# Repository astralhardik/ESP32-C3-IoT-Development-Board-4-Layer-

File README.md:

# ESP32-C3 IoT Development Board (4-Layer)

## 📋 Project Overview

This repository contains the hardware design files (KiCad) for a custom **4-layer IoT Development Board** powered by the **ESP32-C3-WROOM-02** module. 

Designed this compact board is an all-in-one solution for environmental sensing and data logging. It integrates power management for LiPo batteries, a suite of sensors (Environmental, Light, Audio), and dual storage options (SD Card + External Flash), making it ideal for low-power edge computing applications.

## ✨ Key Features

*   **Microcontroller**: ESP32-C3-WROOM-02 (RISC-V 32-bit, WiFi 4 + Bluetooth 5 LE).
*   **4-Layer PCB**: Optimized stack-up for signal integrity and compact routing.
*   **Power System**: 
    *   **USB-C** for power and programming.
    *   **MCP73871** Li-Ion/Li-Poly Battery Charger with System Load Sharing (allows simultaneous charging and system operation).
    *   **LM1117-3.3** LDO for stable 3.3V regulation.
*   **Onboard Sensors**:
    *   **BME280**: Temperature, Humidity, and Barometric Pressure (I2C).
    *   **MAX4466**: Electret Microphone with Preamplifier (Analog Output).
    *   **TEMT6000**: Ambient Light Sensor (Analog Photo-transistor).
*   **Storage**:
    *   **MicroSD Card Slot** (SPI mode).
    *   **W25Q32** 32M-bit (4MB) External SPI Flash for logging/OTA.
*   **Connectivity**:
    *   **CP2102N** USB-to-UART Bridge with Auto-Program/Reset circuit (DTR/RTS logic).
    *   **I2C Header**: JST/Pin header for external OLED displays or sensors.

## 🔧 Hardware Specifications

| Component | Part Number | Interface | Description |
|-----------|-------------|-----------|-------------|
| **MCU Module** | ESP32-C3-WROOM-02-H4 | UART/SPI/I2C | Core processor, 4MB integrated flash |
| **USB Bridge** | CP2102N | USB 2.0 | USB to Serial converter |
| **Env. Sensor** | BME280 | I2C (Add: 0x76) | Precision Temp/Hum/Press |
| **Audio Amp** | MAX4466 | Analog (ADC) | Mic preamp with adjustable gain |
| **Light Sensor** | TEMT6000 | Analog (ADC) | Visible light spectrum sensor |
| **Charger** | MCP73871 | - | 1A Battery charger with Power Path |
| **Ext. Flash** | W25Q32JV | SPI | Additional 32Mbit storage |

## 🔌 Pinout & Interfaces

### User Interface (UI)
*   **Boot Button (SW1)**: Connected to GPIO9 (Strapping pin).
*   **Reset Button (SW2)**: Connected to EN (Enable).
*   **LED Indicators**: 
    *   Charging (Red)
    *   Charged (Green)
    *   Power/User (Blue)

### Expansion Headers
*   **J4 (I2C)**: `3V3`, `SDA`, `SCL`, `GND` - Designed for 0.96" OLED displays.
*   **J5 (GPIO)**: Breakout for spare GPIOs (GPIO8, GPIO18, GPIO19).

## 🛠️ Schematics

### Power Management
The power stage uses the **MCP73871** to manage USB and Battery power seamlessy. An **LM1117-3.3** provides the system voltage.

### Sensor Array
The board features a BME280 for environment data, a MAX4466 for audio processing, and a TEMT6000 for light detection.

### MCU & Storage
The ESP32-C3 is the heart of the board, interfacing with the SD Card and Flash memory via SPI.

## 🚀 Getting Started

1.  **Clone the repository**:
    ```
    git clone https://github.com/yourusername/ESP32-C3-IoT-Board.git
    ```
2.  **Open the Hardware Design**:
    *   Install [KiCad 9.0+](https://www.kicad.org/).
    *   Open `ESP32 project/ESP32 project.kicad_pro`.
3.  **Firmware Development**:
    *   The board uses the **CP2102N** bridge. Ensure drivers are installed.
    *   **PlatformIO / Arduino IDE**: Select board **"ESP32C3 Dev Module"**.
    *   **Auto-Upload**: The board includes the standard transistor reset logic, so no manual button pressing is required to upload code.

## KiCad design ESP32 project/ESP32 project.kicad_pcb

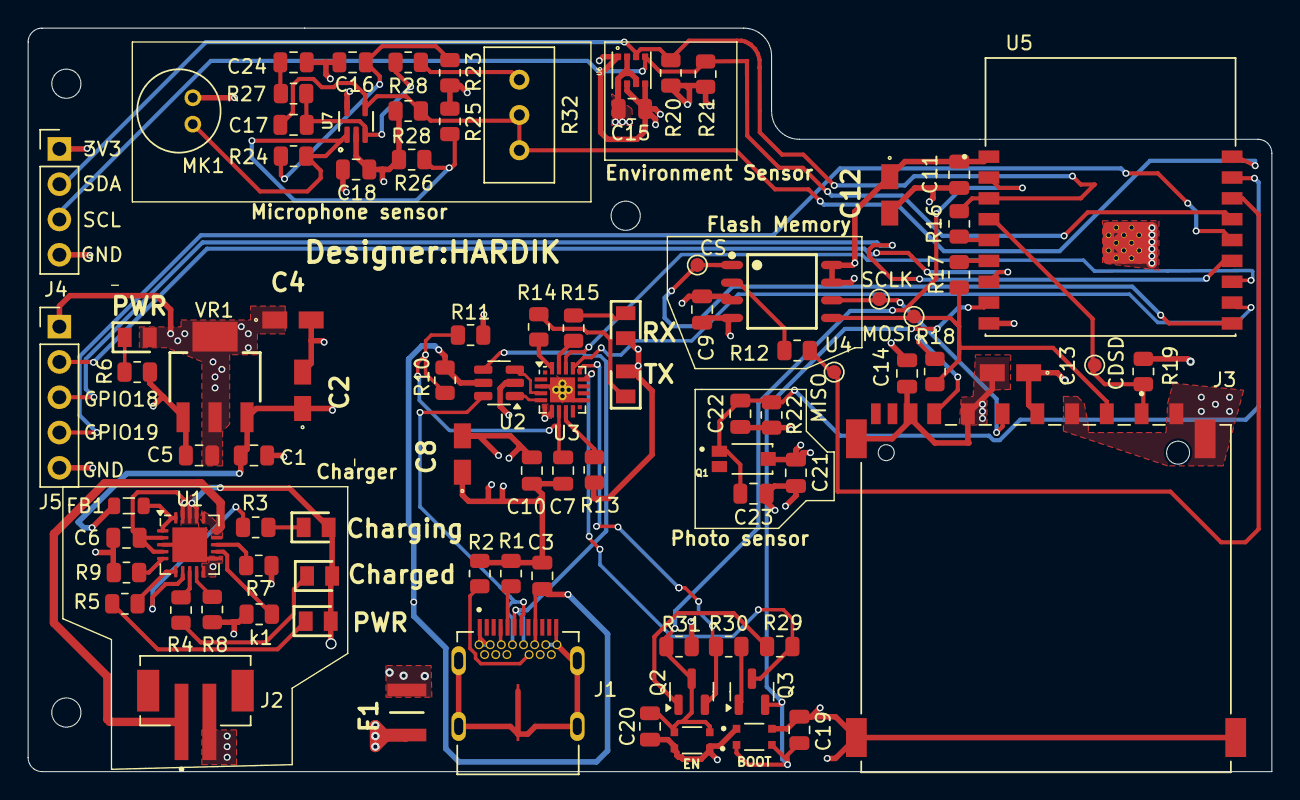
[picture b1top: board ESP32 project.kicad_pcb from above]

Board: 4 copper layers, 89.5 x 53.5 mm, 90 parts (0 on the bottom side), 60 nets.

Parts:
BOOT: Boot; SW_USLPT2819DT2TR
C1, C3, C5, C10, C15, C16, C17, C18, C19, C21: 0.1u; C_0805_2012Metric
C2, C4: 10u; T491A
C6, C20: 1u; C_0805_2012Metric
C7: 1uf; C_0805_2012Metric
C8: 4.7u; T491A
C9, C11, C14: 0.1U; C_0805_2012Metric
C12, C13: 10U; T491A
C22, C23: 10n; C_0805_2012Metric
C24: 10u; C_0805_2012Metric
CDSD: Test CS_SD; TestPoint_Pad_D1.0mm
CS: Test CS; TestPoint_Pad_D1.0mm
Charged: LTST-C170GKT; LEDC2012X120N
Charging: LTST-C170TBKT; LEDC2012X120N
EN: Reset; SW_USLPT2819DT2TR
F1: 0ZCH0110AF2E; FUSC3226X100N
FB1: FerriteBead; L_0805_2012Metric
J1: SS-52400-002; BELFUSE_SS-52400-002
J2: B2B-PH-SM4-TB; JST_B2B-PH-SM4-TB
J3: GSD090012SEU; AMPHENOL_GSD090012SEU
J4: Conn_01x04_Pin; PinHeader_1x04_P2.54mm_Vertical
J5: Conn_01x05_Pin; PinHeader_1x05_P2.54mm_Vertical
MISO: Test MISO; TestPoint_Pad_D1.0mm
MK1: CMC-5042PF-AC; CUI_CMC-5042PF-AC
MOSI: Test MOSI; TestPoint_Pad_D1.0mm
PWR: LTST-C170KRKT; LEDC2012X120N
PWR#2: LTST-C170KRKT; LEDC2012X120N
Q1: TEMT6000X01; TRANS_TEMT6000X01
Q2, Q3: BC817; SOT-23
R1, R2: 5k1; R_0805_2012Metric
R3, R4, R5, R6, R14, R15: 470; R_0805_2012Metric
R7: 2k; R_0805_2012Metric
R8, R9, R22: 10k; R_0805_2012Metric
R10: 22k1; R_0805_2012Metric
R11: 47k5; R_0805_2012Metric
R12, R16, R17, R18: 50; R_0805_2012Metric
R13, R27: 1k; R_0805_2012Metric
R19, R29, R30, R31: 10K; R_0805_2012Metric
R20, R21: 4k7; R_0805_2012Metric
R23, R24: 2K; R_0805_2012Metric
R25, R26: 1M; R_0805_2012Metric
R28: 100K; R_0805_2012Metric
R28#2: 22k; R_0805_2012Metric
R32: 35WR100KLFTR; Potentiometer_Bourns_3296W_Vertical
RX: LTST-C170KRKT; LEDC2012X120N
SCLK: Test SCLK; TestPoint_Pad_D1.0mm
TX: LTST-C170GKT; LEDC2012X120N
U1: MCP73871; QFN-20-1EP_4x4mm_P0.5mm_EP2.5x2.5mm
U2: USBLC6-2SC6; SOT-23-6
U3: CP2102N-Axx-xQFN20; SiliconLabs_QFN-20-1EP_3x3mm_P0.5mm_EP1.8x1.8mm_ThermalVias
U4: W25Q32JVSSIQ; SOIC127P790X216-8N
U5: ESP32-C3-WROOM-02-H4; MODULE_ESP32-C3-WROOM-02-H4
U6: BME280; PSON65P250X250X100-8N
U7: MAX4466EXK; SOT65P210X110-5N
VR1: LM1117MPX-3.3; VREG_LM1117MPX-3.3
k1: 20k; R_0805_2012Metric

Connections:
+3.3V: C4.1, C5.1, C8.2, C9.1, C10.2, C11.1, C12.1, C13.1, C14.1, C15.1, C18.1, C21.2, J3.4 (VDD1), J4.1, J5.1, PWR#2.2 (A), Q1.3, R13.1, R19.1, R20.1, R21.1, R23.1, R25.1, R31.1, RX.2 (A), TX.2 (A), U3.6 (VDD), U3.7 (VREGIN), U4.3 (~WP(IO2)), U4.7 (~HOLD/~RESET(IO3)), U4.8 (VCC), U5.1 (3V3), U6.2 (CSB), U6.6 (VDDIO), U6.8 (VDD), U7.5 (VCC), VR1.2 (VOUT_2), VR1.4 (VOUT_4)
+5V: C1.1, C2.1, FB1.2, VR1.3 (VIN)
/+5v_USB: C6.1, Charged.2 (A), Charging.2 (A), F1.2, PWR.2 (A), U1.2 (VPCC), U1.4 (PROG2), U1.17 (CE), U1.18 (IN), U1.19 (IN)
/ESP32-C3-02/BOOT: BOOT.3 (B0), BOOT.4 (B1), C19.1, Q3.2 (E), U5.8 (IO9)
/ESP32-C3-02/CD_SD: CDSD.1, J3.1 (CD/DAT3), R19.2, U5.4 (IO5)
/ESP32-C3-02/CS: CS.1, U4.1 (~CS), U5.10 (IO10)
/ESP32-C3-02/CTS: Q3.3 (C), R29.1, U3.15 (~CTS)
/ESP32-C3-02/EN: C20.1, EN.3 (B0), EN.4 (B1), Q2.3 (C), R31.2, U5.2 (EN)
/ESP32-C3-02/GPIO8: J5.2, U5.7 (IO8)
/ESP32-C3-02/GPIO18: J5.3, U5.13 (IO18)
/ESP32-C3-02/GPIO19: J5.4, U5.14 (IO19)
/ESP32-C3-02/MIC_OUT: C17.2, R28.2, R32.1, R32.2, U5.18 (IO0), U7.4 (OUT)
/ESP32-C3-02/MISO_DO: MISO.1, R12.2, U5.16 (IO2)
/ESP32-C3-02/MOSI_DI: J3.2 (CMD), MOSI.1, R17.1, R18.1, U4.5 (DI(IO0))
/ESP32-C3-02/PHOTO_C: C22.1, C23.1, Q1.1, R22.1, U5.17 (IO1)
/ESP32-C3-02/RTS: Q2.2 (E), R30.1, U3.16 (~RTS)
/ESP32-C3-02/RX_TX: U3.17 (RXD), U5.11 (RXD)
/ESP32-C3-02/SCL: J4.3, R21.2, U5.15 (IO3), U6.4 (SCK)
/ESP32-C3-02/SCLK: J3.5 (CLK), SCLK.1, U4.6 (CLK)
/ESP32-C3-02/SDA: J4.2, R16.1, R20.2, U5.3 (IO4), U6.3 (SDI)
/ESP32-C3-02/TX_RX: U3.18 (TXD), U5.12 (TXD)
/ESP32-C3-02/USB_D+: U2.3 (I/O2), U3.4 (D+)
/ESP32-C3-02/USB_D-: U2.1 (I/O1), U3.5 (D-)
/USB_DN: J1.A7 (DN1), J1.B7 (DN2), U2.6 (I/O1)
/USB_DP: J1.A6 (DP1), J1.B6 (DP2), U2.4 (I/O2)
/VBAT: J2.1, U1.14 (V_{BAT}), U1.15 (V_{BAT}), U1.16 (V_{BAT_SENSE})
/vBUS: C3.1, F1.1, J1.A4 (VBUSA1), J1.A9 (VBUSA2), J1.B4 (VBUSB1), J1.B9 (VBUSB2), R10.1, U2.5 (VBUS)
GND: BOOT.1 (A0), BOOT.2 (A1), C1.2, C2.2, C3.2, C4.2, C5.2, C6.2, C7.2, C8.1, C9.2, C10.1, C11.2, C12.2, C13.2, C14.2, C15.2, C16.1, C18.2, C19.2, C20.2, C21.1, C22.2, C23.2, C24.1, EN.1 (A0), EN.2 (A1), J1.A1 (GNDA1), J1.A12 (GNDA2), J1.B1 (GNDB1), J1.B12 (GNDB2), J1.G1 (GND/SHIELD), J1.G2 (GND/SHIELD), J1.G3 (GND/SHIELD), J1.G4 (GND/SHIELD), J1.S1 (GND/SHIELD), J1.S2 (GND/SHIELD), J1.S3 (GND/SHIELD), J1.S4 (GND/SHIELD), J2.2, J3.3 (VSS1), J3.6 (VSS2), J3.8 (DAT1), J3.9 (DAT2), J3.G1 (SHIELD_GND), J3.G2 (SHIELD_GND), J3.G3 (SHIELD_GND), J3.G4 (SHIELD_GND), J4.4, J5.5, MK1.GND, R1.2, R2.2, R6.2, R7.1, R8.2, R9.1, R11.2, R22.2, R26.2, R28.1, U1.3 (SEL), U1.10 (V_{SS}), U1.11 (V_{SS}), U1.21 (V_{SS}), U2.2 (GND), U4.4 (GND), U5.9 (GND), U5.19 (GND), U5.20 (GND), U5.21 (GND), U5.22 (GND), U5.23 (GND), U5.24 (GND), U5.25 (GND), U5.26 (GND), U5.27 (GND), U5.28 (GND), U5.29 (GND), U5.30 (GND), U5.31 (GND), U5.32 (GND), U5.33 (GND), U5.34 (GND), U5.35 (GND), U5.36 (GND), U5.37 (GND), U5.38 (GND), U5.39 (GND), U6.1 (GND), U6.5 (SDO), U6.7 (GND), U7.2 (GND), VR1.1 (GND), k1.1
unnamed: C16.2, R23.2, R24.1
unnamed: C24.2, R27.1
unnamed: FB1.1, U1.1 (OUT), U1.20 (OUT)
unnamed: J1.A5 (CC1), R1.1
unnamed: J1.B5 (CC2), R2.1
unnamed: J3.7 (DAT0), R18.2
unnamed: Charging.1 (K), R3.1
unnamed: PWR#2.1 (K), R6.1
unnamed: Charged.1 (K), R4.1
unnamed: PWR.1 (K), R5.1
unnamed: R14.1, TX.1 (K)
unnamed: R15.1, RX.1 (K)
unnamed: Q2.1 (B), R29.2
unnamed: Q3.1 (B), R30.2
unnamed: R28#2.1, R32.3
unnamed: R7.2, U1.13 (PROG1)
unnamed: U1.12 (PROG3), k1.2
unnamed: R4.2, U1.8 (STAT1/~LBO)
unnamed: R3.2, U1.7 (STAT2)
unnamed: R9.2, U1.5 (THERM)
unnamed: R5.2, U1.6 (~PG)
unnamed: R8.1, U1.9 (~TE)
unnamed: U3.3 (GND), U3.12 (GND), U3.21 (GND)
unnamed: C7.1, R10.2, R11.1, U3.8 (VBUS)
unnamed: R13.2, U3.9 (~RST)
unnamed: R15.2, U3.19 (~RXT/GPIO.3)
unnamed: R14.2, U3.20 (~TXT/GPIO.2)
unnamed: R12.1, U4.2 (DO(IO1))
unnamed: R16.2, U5.5 (IO6)
unnamed: R17.2, U5.6 (IO7)
unnamed: MK1.OUT, R24.2, R25.2, R26.1, U7.1 (IN+)
unnamed: C17.1, R27.2, R28#2.2, U7.3 (IN-)

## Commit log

2025-11-30 Initial upload
2025-11-30 README.md

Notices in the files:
README.md:
License: MIT
